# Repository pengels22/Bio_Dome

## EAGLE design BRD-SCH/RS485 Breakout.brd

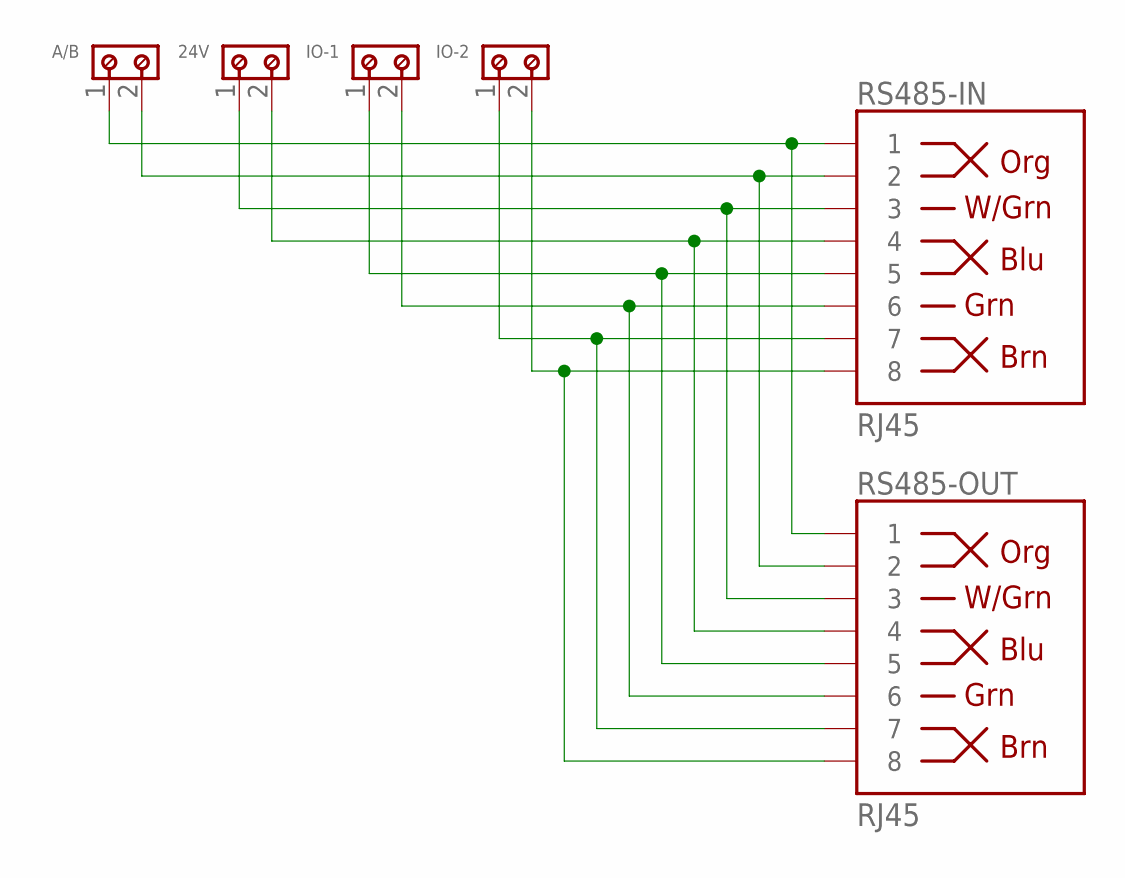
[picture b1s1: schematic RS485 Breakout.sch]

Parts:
24V: 691201520002
A/B: 691201520002
IO-1, IO-2: 691201520002
RS485-IN, RS485-OUT: RJ45; RJ45-8

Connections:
+24: 24V.1, RS485-IN.3, RS485-OUT.3
-24: 24V.2, RS485-IN.4, RS485-OUT.4
A: A/B.1, RS485-IN.1, RS485-OUT.1
B: A/B.2, RS485-IN.2, RS485-OUT.2
IO0: IO-1.2, RS485-IN.6, RS485-OUT.6
IO1: IO-1.1, RS485-IN.5, RS485-OUT.5
IO2: IO-2.2, RS485-IN.8, RS485-OUT.8
IO3: IO-2.1, RS485-IN.7, RS485-OUT.7

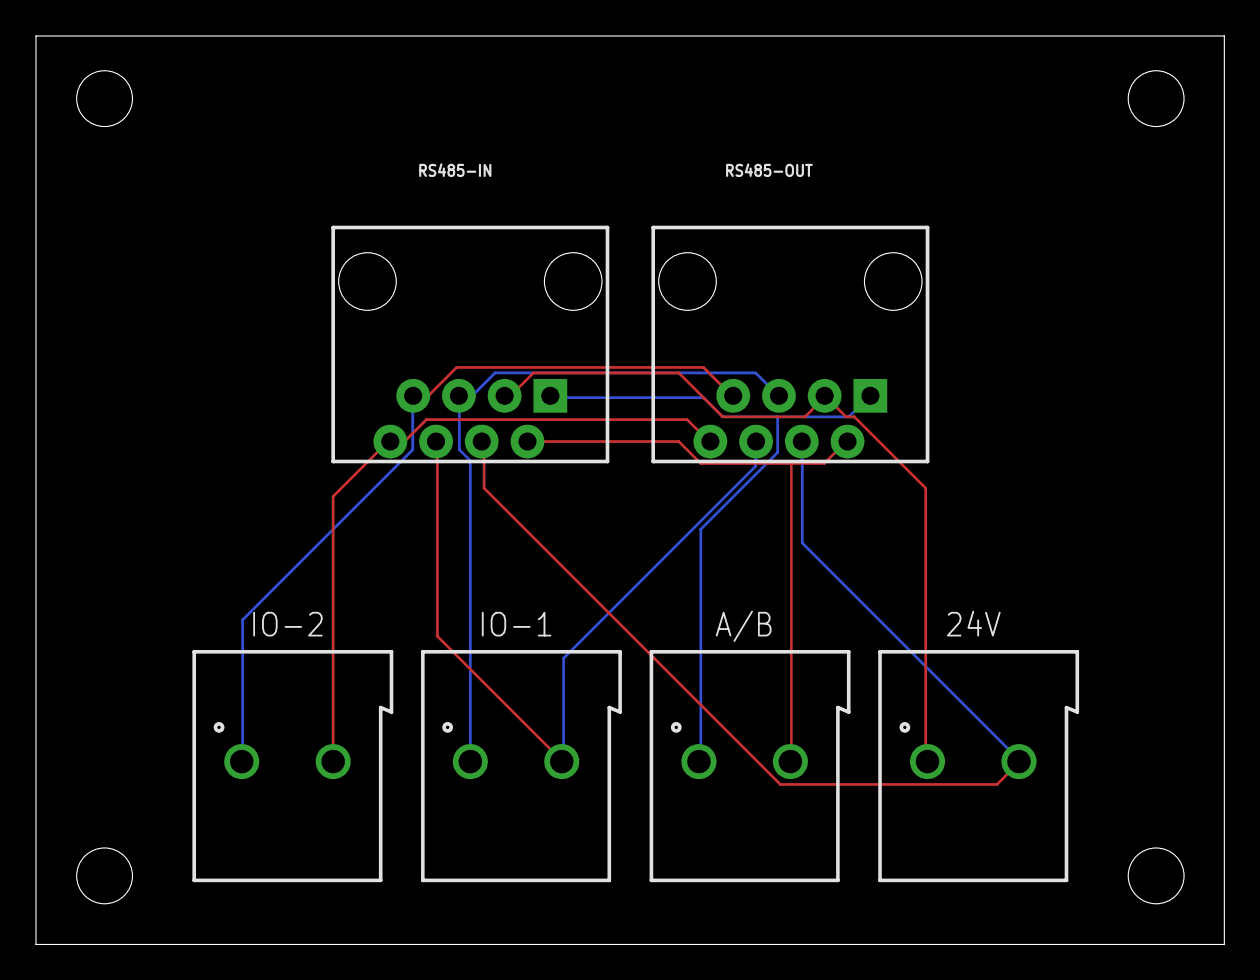
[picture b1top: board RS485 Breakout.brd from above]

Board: 2 copper layers, 66.0 x 50.5 mm, 6 parts (0 on the bottom side), 8 nets.

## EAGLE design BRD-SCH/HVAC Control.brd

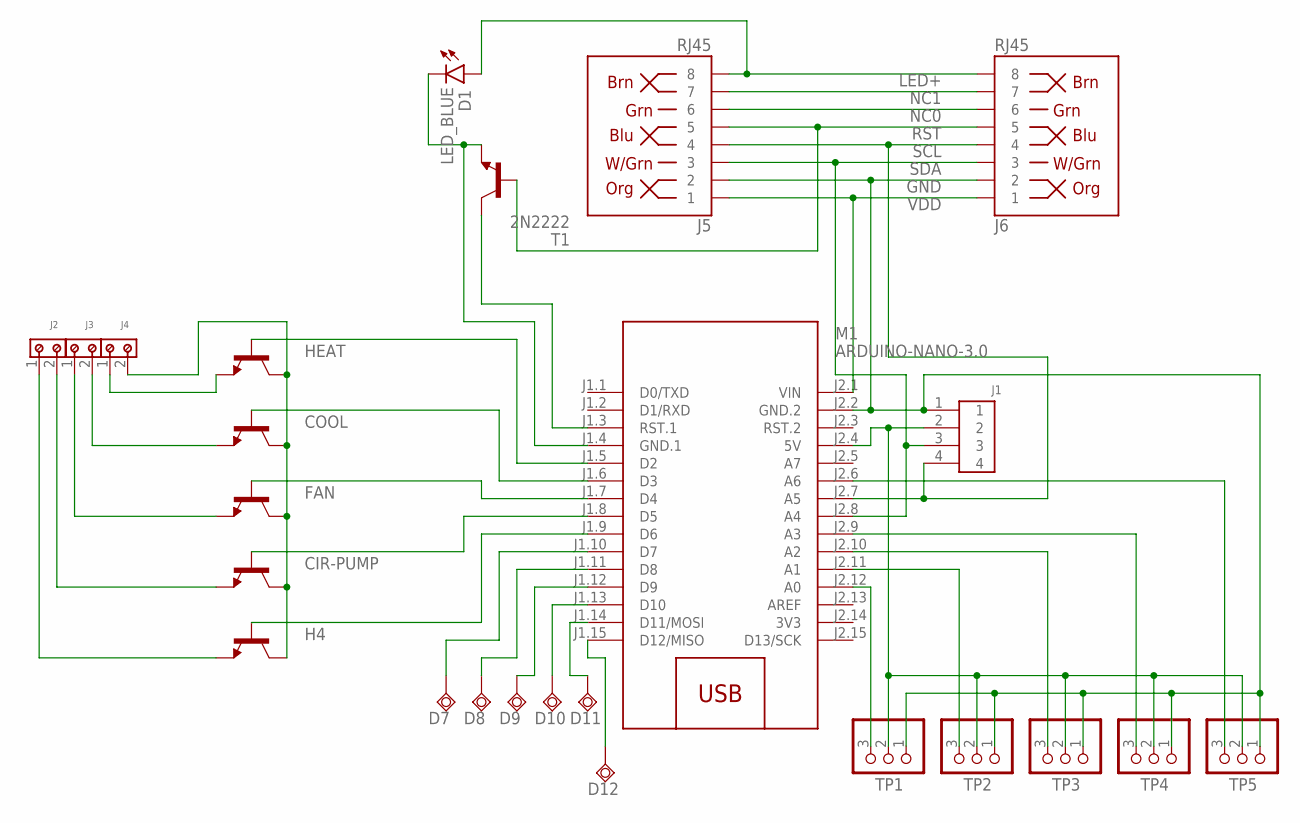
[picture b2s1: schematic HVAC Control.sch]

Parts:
CIR-PUMP: 600mA/40V; TO-92
COOL: 600mA/40V; TO-92
D1: LED_BLUE; LEDRD254W60D565H860B_B
D7, D8, D9, D10, D11, D12: TESTPAD_TPSQPAD1-13; TESTPAD_P1-13
FAN: 600mA/40V; TO-92
H4: 600mA/40V; TO-92
HEAT: 600mA/40V; TO-92
J1: B4B-XH-A(LF)(SN)
J2, J3, J4: 691201820002
J5, J6: RJ45; RJ45-8
M1: ARDUINO-NANO-3.0
T1: 2N2222; TO18
TP1, TP2, TP3, TP4, TP5: PINHD-1X3; 1X03

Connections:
3V3: M1.J2.14 (3V3)
GND: J1.1, J5.2, J6.2, M1.J2.2 (GND.2), M1.J2.3 (RST.2), TP1.1, TP2.1, TP3.1, TP4.1, TP5.1
LED+: D1.1 (A), J5.8, J6.8
unnamed: D7.TP, M1.J1.10 (D7)
unnamed: J1.2, M1.J2.4 (5V), TP1.2, TP2.2, TP3.2, TP4.2, TP5.2
unnamed: D8.TP, M1.J1.11 (D8)
unnamed: D9.TP, M1.J1.12 (D9)
unnamed: HEAT.2 (B), M1.J1.5 (D2)
unnamed: COOL.2 (B), M1.J1.6 (D3)
unnamed: FAN.2 (B), M1.J1.7 (D4)
unnamed: CIR-PUMP.2 (B), M1.J1.8 (D5)
unnamed: H4.2 (B), M1.J1.9 (D6)
unnamed: CIR-PUMP.1 (C), COOL.1 (C), FAN.1 (C), H4.1 (C), HEAT.1 (C), J4.2
unnamed: H4.3 (E), J2.1
unnamed: CIR-PUMP.3 (E), J2.2
unnamed: FAN.3 (E), J3.1
unnamed: COOL.3 (E), J3.2
unnamed: HEAT.3 (E), J4.1
unnamed: M1.J2.12 (A0), TP1.3
unnamed: M1.J2.11 (A1), TP2.3
unnamed: M1.J2.10 (A2), TP3.3
unnamed: M1.J2.9 (A3), TP4.3
unnamed: M1.J2.6 (A6), TP5.3
unnamed: M1.J1.3 (RST.1), T1.3 (C)
unnamed: D1.2 (C), M1.J1.4 (GND.1), T1.1 (E)
unnamed: D10.TP, M1.J1.13 (D10)
unnamed: D11.TP, M1.J1.14 (D11/MOSI)
unnamed: D12.TP, M1.J1.15 (D12/MISO)
NC0: J5.6, J6.6
NC1: J5.7, J6.7
RST: J5.5, J6.5, T1.2 (B)
SCL: J1.4, J5.4, J6.4, M1.J2.7 (A5)
SDA: J1.3, J5.3, J6.3, M1.J2.8 (A4)
VDD: J5.1, J6.1, M1.J2.1 (VIN)

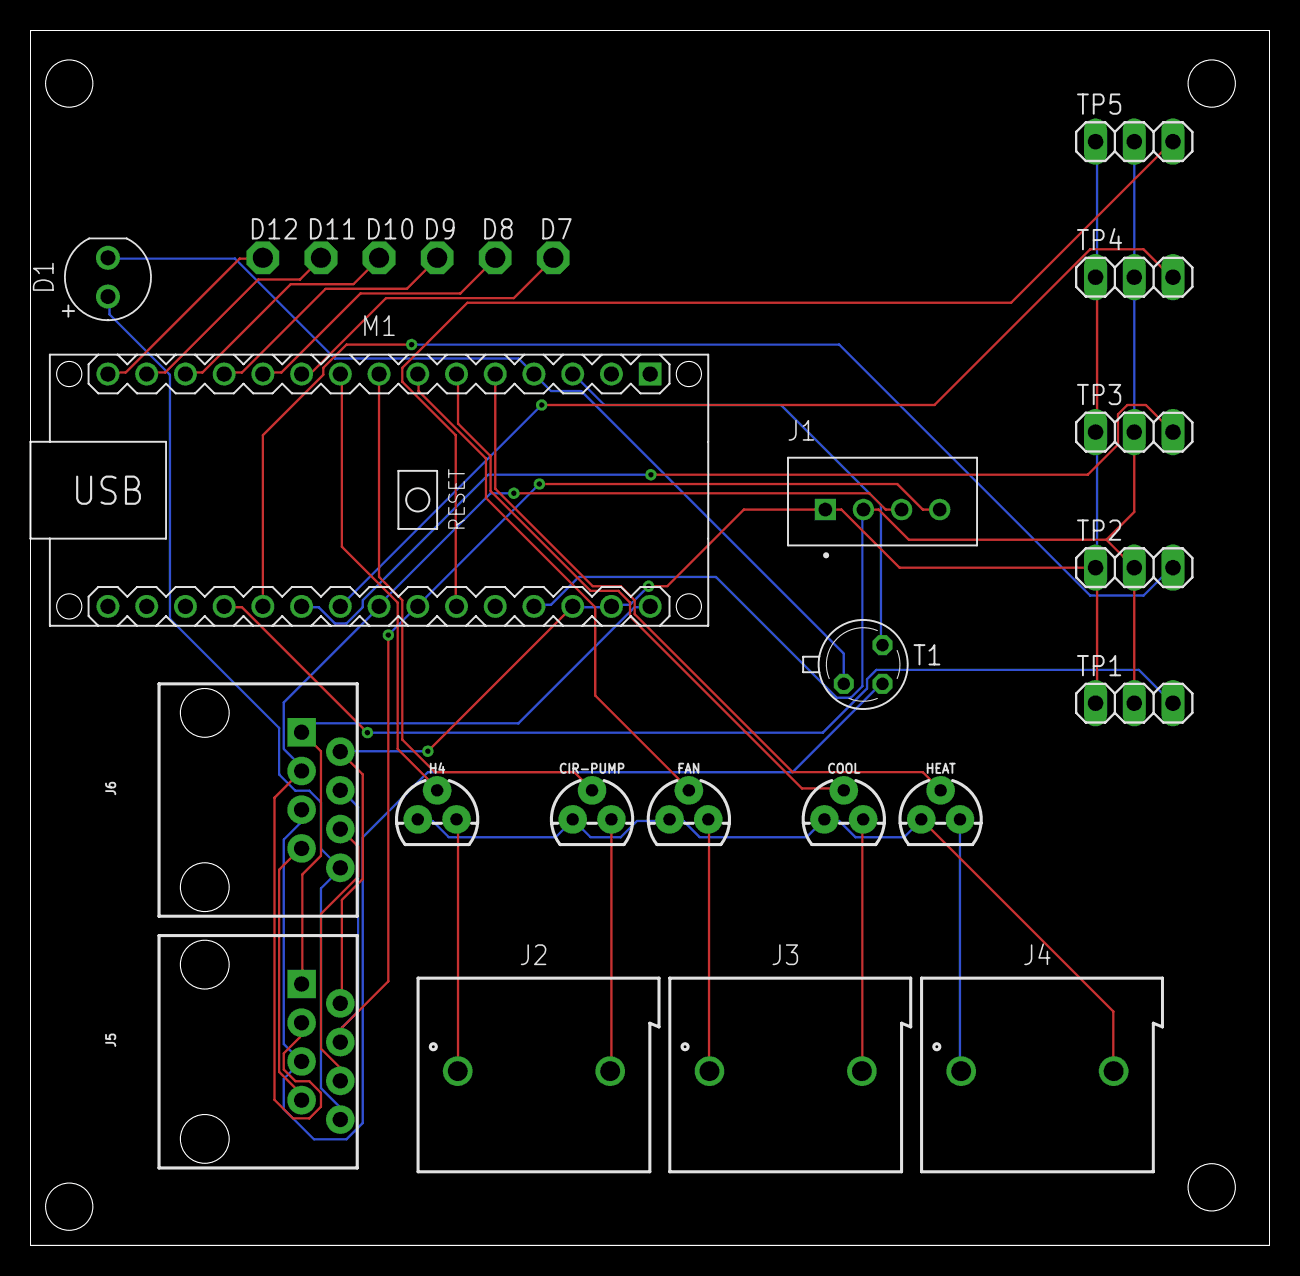
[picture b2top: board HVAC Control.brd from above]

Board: 2 copper layers, 81.3 x 79.7 mm, 25 parts (0 on the bottom side), 33 nets.

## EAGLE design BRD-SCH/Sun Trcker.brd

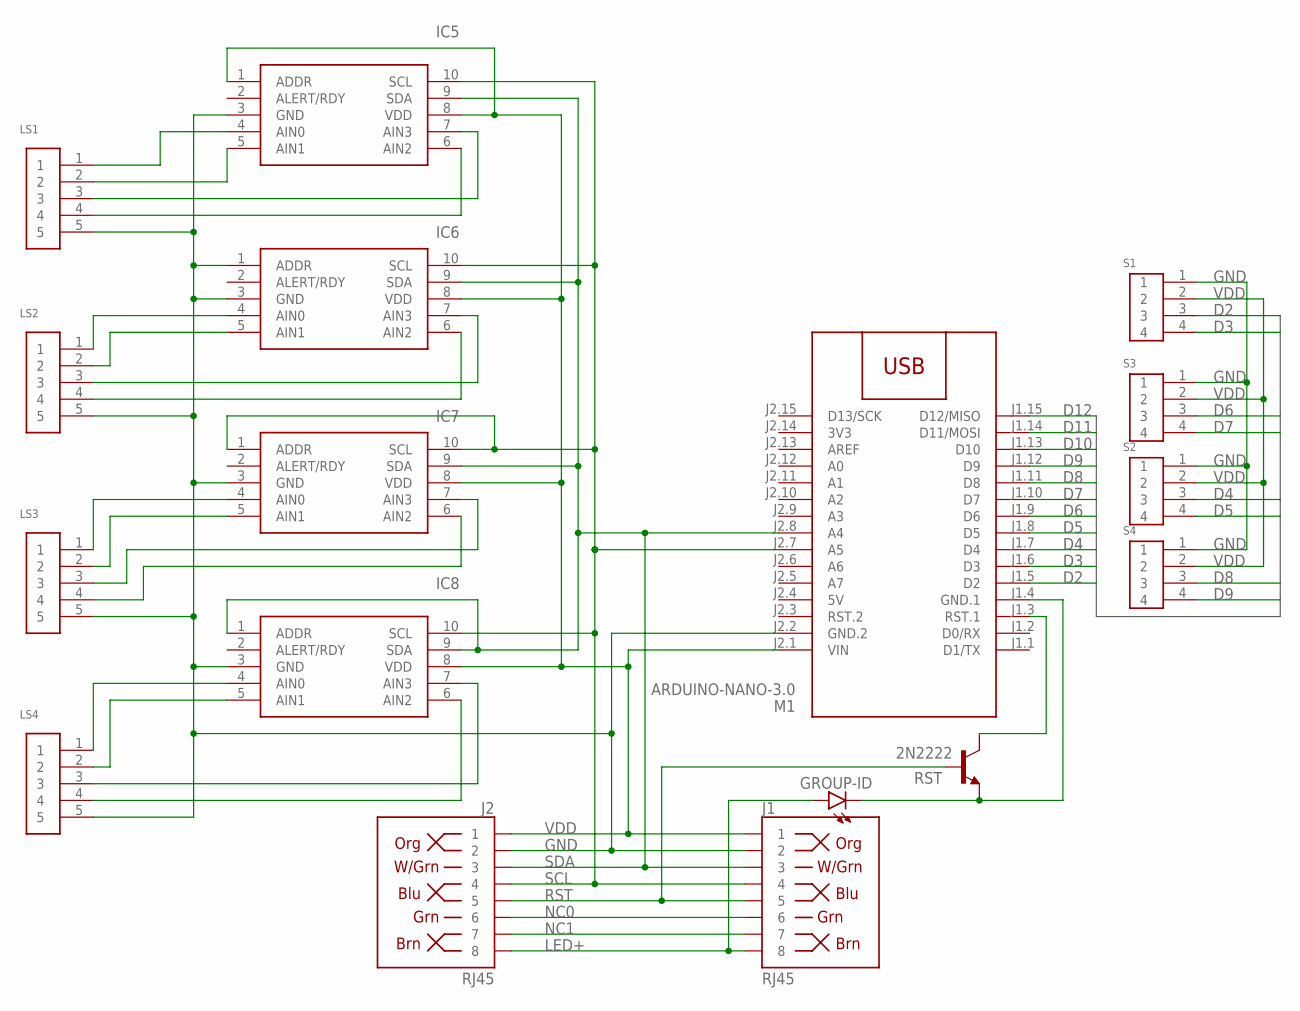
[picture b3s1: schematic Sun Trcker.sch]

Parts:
GROUP-ID: LED_BLUE; LEDRD254W60D565H860B_B
IC5, IC6, IC7, IC8: ADS1115IDGST; SOP50P490X110-10N
J1, J2: RJ45; RJ45-8
LS1, LS2, LS3, LS4: S5B-EH(LF)(SN)
M1: ARDUINO-NANO-3.0
RST: 2N2222; TO18
S1, S2, S3, S4: B4B-XH-A(LF)(SN)

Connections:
3V3: M1.J2.14 (3V3)
5V: M1.J2.4 (5V)
D2: M1.J1.5 (D2), S1.3
D3: M1.J1.6 (D3), S1.4
D4: M1.J1.7 (D4), S2.3
D5: M1.J1.8 (D5), S2.4
D6: M1.J1.9 (D6), S3.3
D7: M1.J1.10 (D7), S3.4
D8: M1.J1.11 (D8), S4.3
D9: M1.J1.12 (D9), S4.4
D10: M1.J1.13 (D10)
D11: M1.J1.14 (D11/MOSI)
D12: M1.J1.15 (D12/MISO)
GND: IC5.3 (GND), IC6.1 (ADDR), IC6.3 (GND), IC7.3 (GND), IC8.3 (GND), J1.2, J2.2, LS1.5, LS2.5, LS3.5, LS4.5, M1.J2.2 (GND.2), S1.1, S2.1, S3.1, S4.1
LED+: GROUP-ID.1 (A), J1.8, J2.8
unnamed: IC5.4 (AIN0), LS1.1
unnamed: IC5.5 (AIN1), LS1.2
unnamed: IC5.7 (AIN3), LS1.3
unnamed: IC5.6 (AIN2), LS1.4
unnamed: GROUP-ID.2 (C), M1.J1.4 (GND.1), RST.1 (E)
unnamed: IC6.4 (AIN0), LS2.1
unnamed: M1.J1.3 (RST.1), RST.3 (C)
unnamed: IC6.5 (AIN1), LS2.2
unnamed: IC6.7 (AIN3), LS2.3
unnamed: IC6.6 (AIN2), LS2.4
unnamed: IC7.4 (AIN0), LS3.1
unnamed: IC7.5 (AIN1), LS3.2
unnamed: IC7.7 (AIN3), LS3.3
unnamed: IC7.6 (AIN2), LS3.4
unnamed: IC8.4 (AIN0), LS4.1
unnamed: IC8.5 (AIN1), LS4.2
unnamed: IC8.7 (AIN3), LS4.3
unnamed: IC8.6 (AIN2), LS4.4
NC0: J1.6, J2.6
NC1: J1.7, J2.7
RST: J1.5, J2.5, RST.2 (B)
SCL: IC5.10 (SCL), IC6.10 (SCL), IC7.1 (ADDR), IC7.10 (SCL), IC8.10 (SCL), J1.4, J2.4, M1.J2.7 (A5)
SDA: IC5.9 (SDA), IC6.9 (SDA), IC7.9 (SDA), IC8.1 (ADDR), IC8.9 (SDA), J1.3, J2.3, M1.J2.8 (A4)
VDD: IC5.1 (ADDR), IC5.8 (VDD), IC6.8 (VDD), IC7.8 (VDD), IC8.8 (VDD), J1.1, J2.1, M1.J2.1 (VIN), S1.2, S2.2, S3.2, S4.2

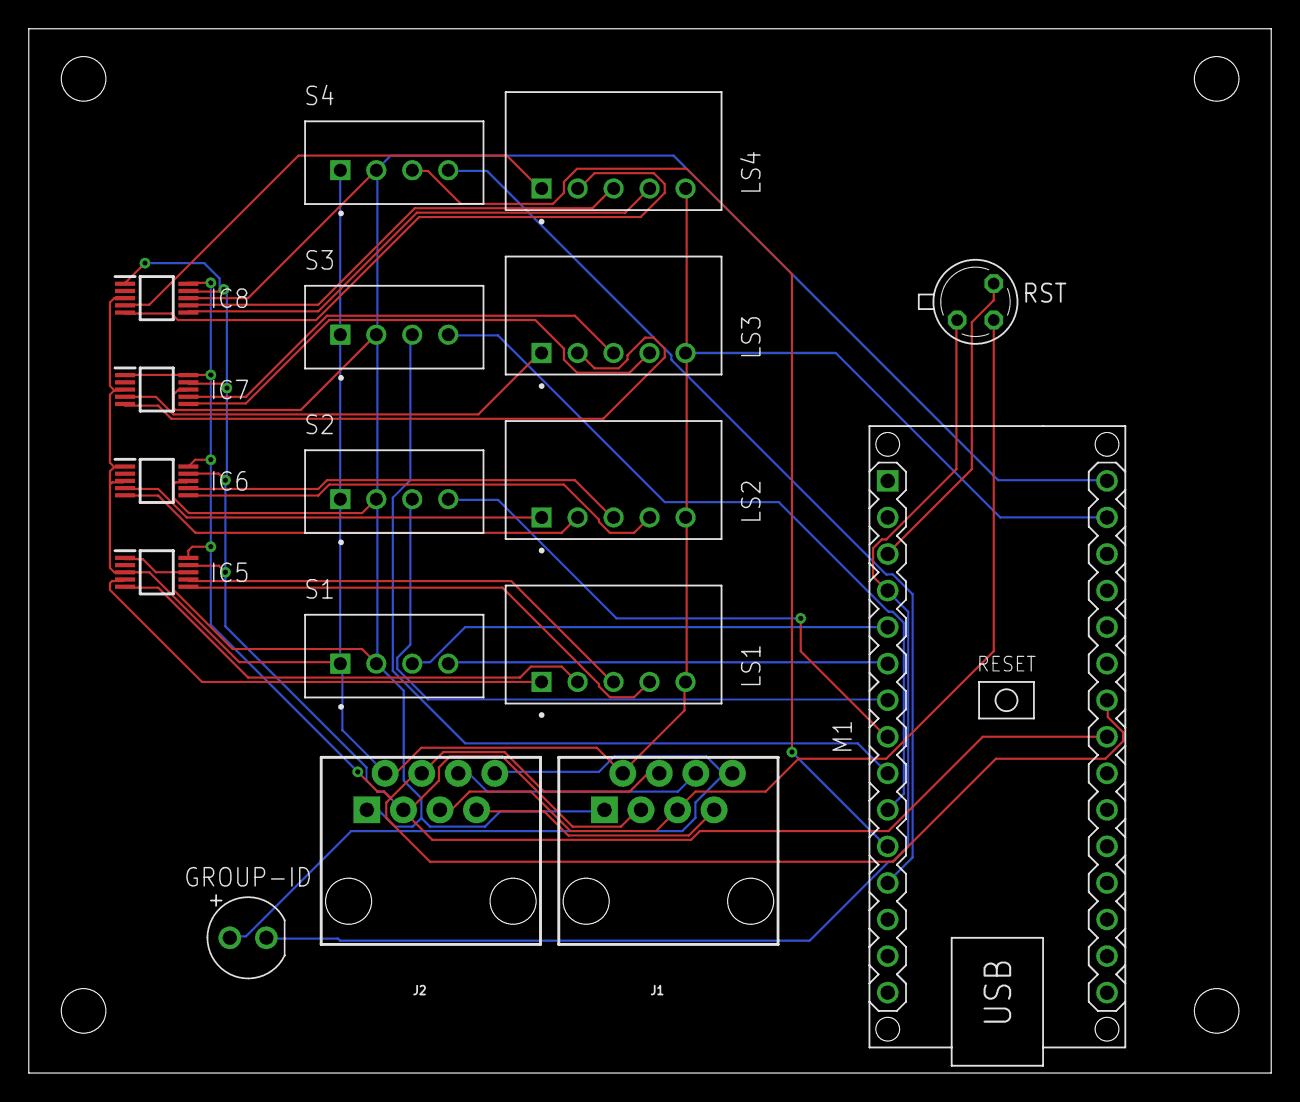
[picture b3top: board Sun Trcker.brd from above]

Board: 2 copper layers, 86.3 x 72.6 mm, 17 parts (0 on the bottom side), 34 nets.

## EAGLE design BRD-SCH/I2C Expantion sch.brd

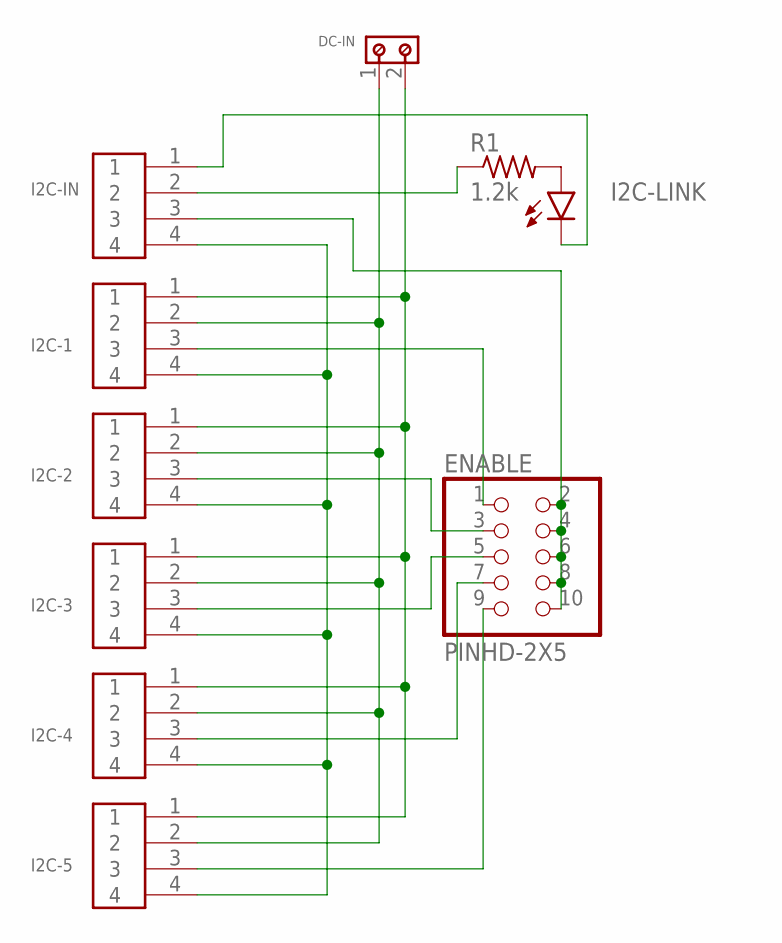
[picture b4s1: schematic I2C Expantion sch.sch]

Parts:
DC-IN: 691201620002
ENABLE: PINHD-2X5; 2X05
I2C-1, I2C-2, I2C-3, I2C-4, I2C-5, I2C-IN: B4B-XH-A(LF)(SN)
I2C-LINK: LED_BLUE; LEDRD254W60D565H860B_B
R1: 1.2k; RESAD724W46L381D178B

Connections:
GND: DC-IN.2, I2C-1.1, I2C-2.1, I2C-3.1, I2C-4.1, I2C-5.1
unnamed: I2C-LINK.1 (A), R1.2
unnamed: I2C-IN.2, R1.1
unnamed: I2C-IN.1, I2C-LINK.2 (C)
unnamed: ENABLE.9, I2C-5.3
unnamed: ENABLE.7, I2C-4.3
unnamed: ENABLE.5, I2C-3.3
unnamed: ENABLE.3, I2C-2.3
unnamed: ENABLE.1, I2C-1.3
SCL: I2C-1.4, I2C-2.4, I2C-3.4, I2C-4.4, I2C-5.4, I2C-IN.4
SDA: ENABLE.2, ENABLE.4, ENABLE.6, ENABLE.8, ENABLE.10, I2C-IN.3
VCC: DC-IN.1, I2C-1.2, I2C-2.2, I2C-3.2, I2C-4.2, I2C-5.2

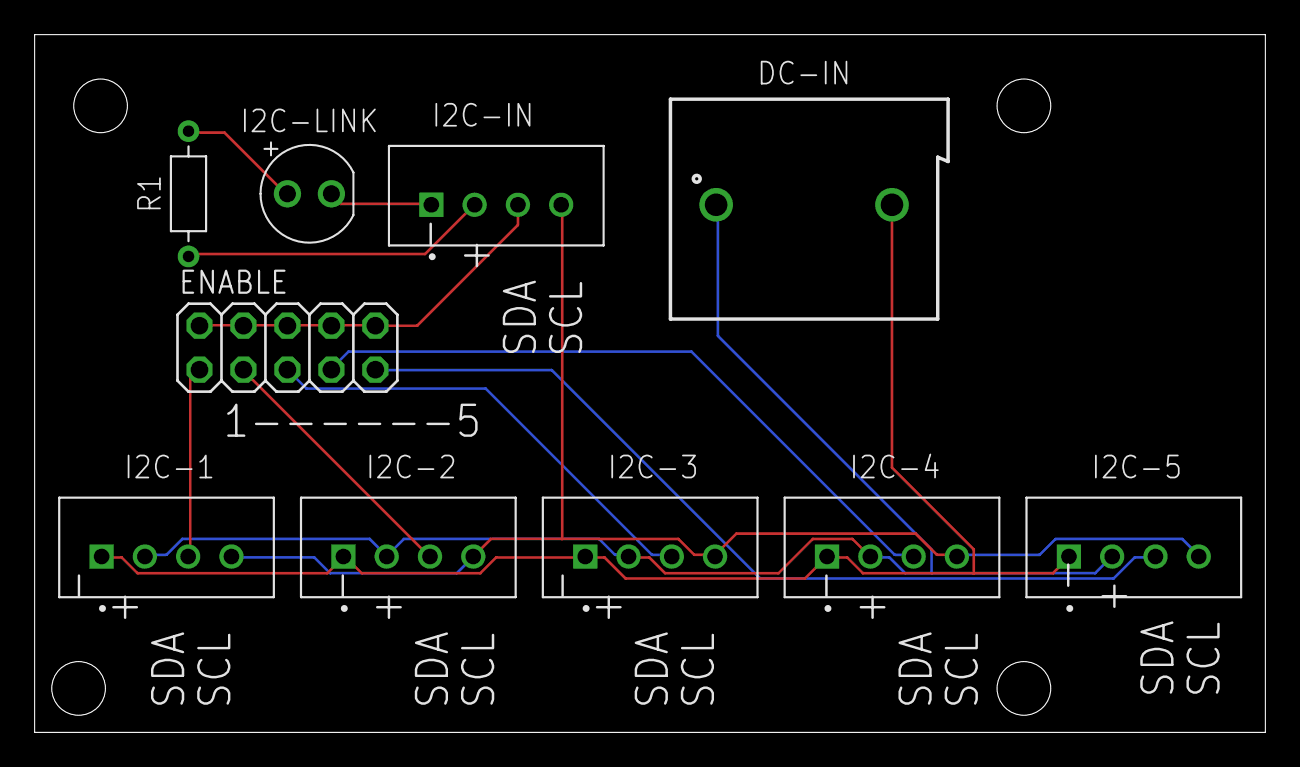
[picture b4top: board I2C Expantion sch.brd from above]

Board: 2 copper layers, 71.1 x 40.3 mm, 10 parts (0 on the bottom side), 12 nets.

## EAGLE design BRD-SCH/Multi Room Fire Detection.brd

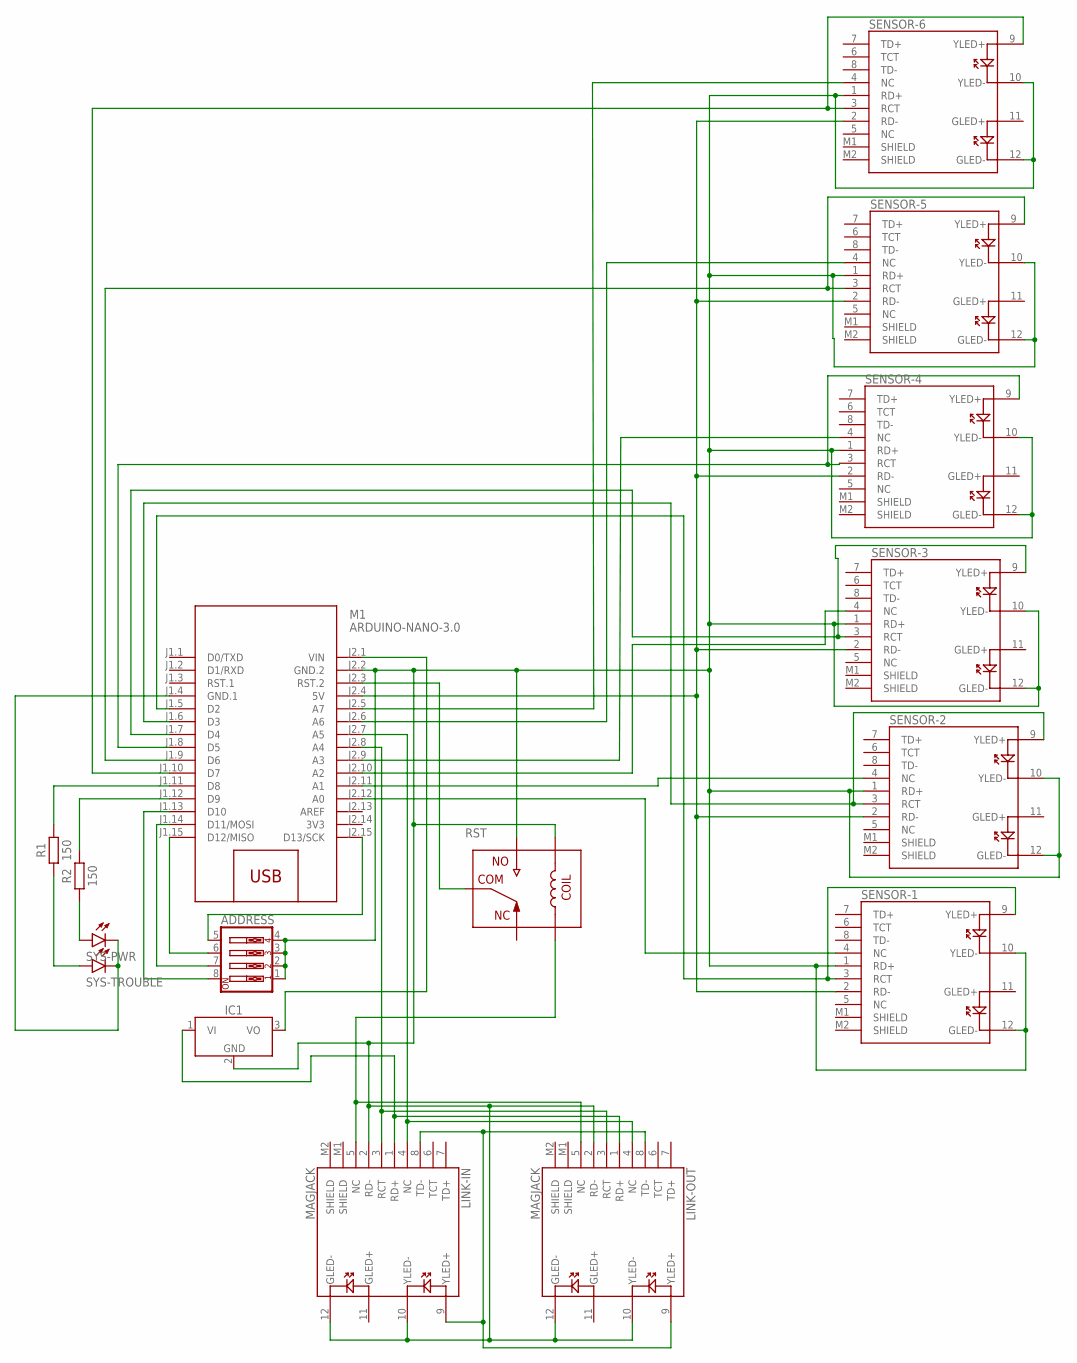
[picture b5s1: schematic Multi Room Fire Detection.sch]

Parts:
ADDRESS: SW_DIP-4; EDG-04
IC1: LM7805_TO220V; TO220V
LINK-IN: MAGJACK
LINK-OUT: MAGJACK
M1: ARDUINO-NANO-3.0
R1, R2: 150; RESAD724W46L381D178B
RST: ACT112
SENSOR-1, SENSOR-2, SENSOR-3, SENSOR-4, SENSOR-5, SENSOR-6: MAGJACK
SYS-PWR: LED_GREEN; LEDRD254W60D565H860B_G
SYS-TROUBLE: LED_RED; LEDRD254W60D565H860B

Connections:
3V3: M1.J2.14 (3V3)
GND: ADDRESS.1, ADDRESS.2, ADDRESS.3, ADDRESS.4, IC1.2 (GND), LINK-IN.2 (RD-), LINK-IN.10 (YLED-), LINK-IN.12 (GLED-), LINK-OUT.2 (RD-), LINK-OUT.10 (YLED-), LINK-OUT.12 (GLED-), M1.J2.2 (GND.2), RST.1, RST.4, SENSOR-1.1 (RD+), SENSOR-1.10 (YLED-), SENSOR-1.12 (GLED-), SENSOR-2.1 (RD+), SENSOR-2.10 (YLED-), SENSOR-2.12 (GLED-), SENSOR-3.1 (RD+), SENSOR-3.10 (YLED-), SENSOR-3.12 (GLED-), SENSOR-4.1 (RD+), SENSOR-4.10 (YLED-), SENSOR-4.12 (GLED-), SENSOR-5.1 (RD+), SENSOR-5.10 (YLED-), SENSOR-5.12 (GLED-), SENSOR-6.1 (RD+), SENSOR-6.10 (YLED-), SENSOR-6.12 (GLED-)
unnamed: M1.J2.12 (A0), SENSOR-1.4 (NC)
unnamed: M1.J2.11 (A1), SENSOR-2.4 (NC)
unnamed: M1.J2.10 (A2), SENSOR-3.4 (NC)
unnamed: M1.J2.9 (A3), SENSOR-4.4 (NC)
unnamed: M1.J2.6 (A6), SENSOR-5.4 (NC)
unnamed: M1.J2.5 (A7), SENSOR-6.4 (NC)
unnamed: M1.J1.10 (D7), SENSOR-6.3 (RCT), SENSOR-6.9 (YLED+)
unnamed: M1.J1.9 (D6), SENSOR-5.3 (RCT), SENSOR-5.9 (YLED+)
unnamed: M1.J1.8 (D5), SENSOR-4.3 (RCT), SENSOR-4.9 (YLED+)
unnamed: M1.J1.7 (D4), SENSOR-3.3 (RCT), SENSOR-3.9 (YLED+)
unnamed: M1.J1.6 (D3), SENSOR-2.3 (RCT), SENSOR-2.9 (YLED+)
unnamed: M1.J1.5 (D2), SENSOR-1.3 (RCT), SENSOR-1.9 (YLED+)
unnamed: M1.J2.4 (5V), SENSOR-1.2 (RD-), SENSOR-2.2 (RD-), SENSOR-3.2 (RD-), SENSOR-4.2 (RD-), SENSOR-5.2 (RD-), SENSOR-6.2 (RD-)
unnamed: M1.J2.3 (RST.2), RST.2
unnamed: LINK-IN.3 (RCT), LINK-OUT.3 (RCT), M1.J2.8 (A4)
unnamed: LINK-IN.4 (NC), LINK-OUT.4 (NC), M1.J2.7 (A5)
unnamed: LINK-IN.5 (NC), LINK-OUT.5 (NC), RST.5
unnamed: M1.J1.11 (D8), R1.2
unnamed: M1.J1.12 (D9), R2.2
unnamed: R1.1, SYS-TROUBLE.1 (A)
unnamed: M1.J1.4 (GND.1), SYS-PWR.2 (C), SYS-TROUBLE.2 (C)
unnamed: R2.1, SYS-PWR.1 (A)
unnamed: ADDRESS.5, M1.J2.15 (D13/SCK)
unnamed: ADDRESS.6, M1.J1.15 (D12/MISO)
unnamed: ADDRESS.7, M1.J1.14 (D11/MOSI)
unnamed: ADDRESS.8, M1.J1.13 (D10)
unnamed: LINK-IN.8 (TD-), LINK-IN.9 (YLED+), LINK-OUT.8 (TD-), LINK-OUT.9 (YLED+)
VI: IC1.1 (VI), LINK-IN.1 (RD+), LINK-OUT.1 (RD+)
VO: IC1.3 (VO), M1.J2.1 (VIN)

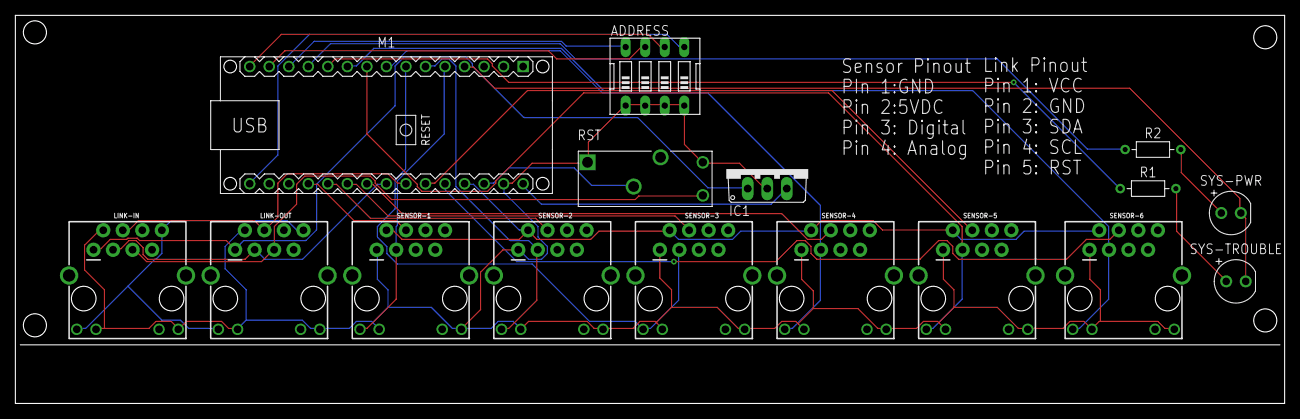
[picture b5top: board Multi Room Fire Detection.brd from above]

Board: 2 copper layers, 165.1 x 50.5 mm, 16 parts (0 on the bottom side), 30 nets.

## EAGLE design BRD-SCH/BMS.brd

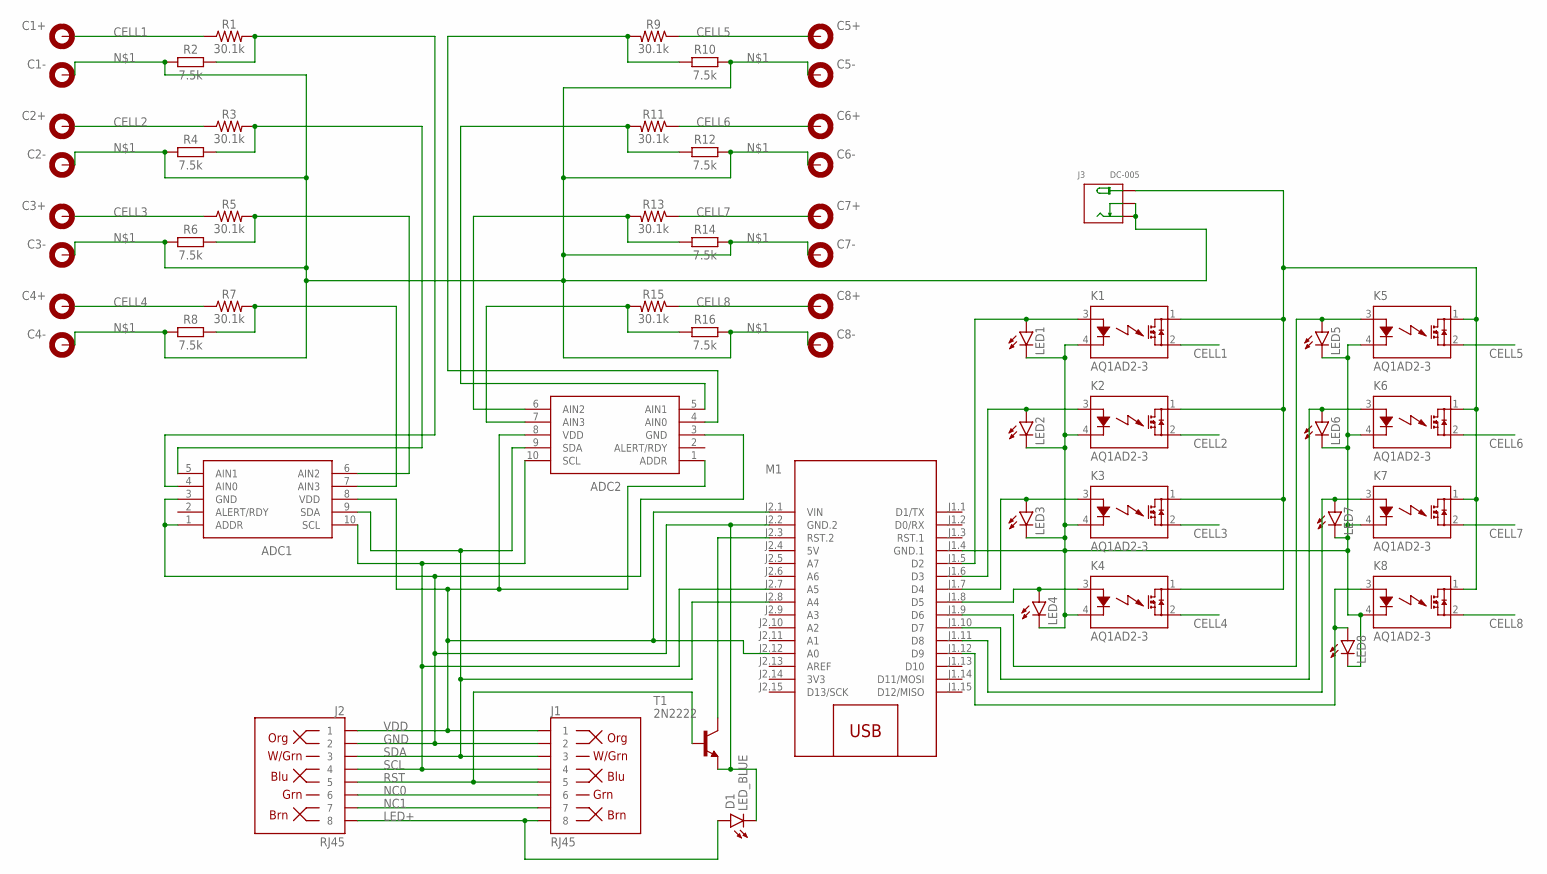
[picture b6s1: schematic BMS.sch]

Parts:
ADC1, ADC2: ADS1115IDGST; SOP50P490X110-10N
C1+, C1-, C2+, C2-, C3+, C3-, C4+, C4-, C5+, C5-, C6+, C6-, C7+, C7-, C8+, C8-: HOLES_MOUNT-PAD-ROUND-0.096-NS; HOLES_096-PAD-NS
D1: LED_BLUE; LEDRD254W60D565H860B_B
J1, J2: RJ45; RJ45-8
J3: DC-005; DCJ3P-14.2X11.0X9.0MM
K1, K2, K3, K4, K5, K6, K7, K8: AQ1AD2-3; AQ1
LED1, LED2, LED3, LED4, LED5, LED6, LED7, LED8: LEDCHIP-LED0805; CHIP-LED0805
M1: ARDUINO-NANO-3.0
R1, R3, R5, R7, R9, R11, R13, R15: 30.1k; 0603
R2, R4, R6, R8, R10, R12, R14, R16: 7.5k; RESC3216X70
T1: 2N2222; TO18

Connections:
3V3: M1.J2.14 (3V3)
5V: M1.J2.4 (5V)
C+: J3.+B (+), J3.+T (+), K1.1 (DS1), K2.1 (DS1), K3.1 (DS1), K4.1 (DS1), K5.1 (DS1), K6.1 (DS1), K7.1 (DS1), K8.1 (DS1)
CELL1: C1+.B096, K1.2 (DS2), R1.1
CELL2: C2+.B096, K2.2 (DS2), R3.1
CELL3: C3+.B096, K3.2 (DS2), R5.1
CELL4: C4+.B096, K4.2 (DS2), R7.1
CELL5: C5+.B096, K5.2 (DS2), R9.1
CELL6: C6+.B096, K6.2 (DS2), R11.1
CELL7: C7+.B096, K7.2 (DS2), R13.1
CELL8: C8+.B096, K8.2 (DS2), R15.1
GND: ADC1.1 (ADDR), ADC1.3 (GND), ADC2.3 (GND), D1.2 (C), J1.2, J2.2, M1.J2.2 (GND.2), T1.1 (E)
LED+: D1.1 (A), J1.8, J2.8
unnamed: C1-.B096, C2-.B096, C3-.B096, C4-.B096, C5-.B096, C6-.B096, C7-.B096, C8-.B096, J3.-1B (-), J3.-1T (-), J3.-2 (CDN), J3.-2B (CDN), R2.1, R4.1, R6.1, R8.1, R10.1, R12.1, R14.1, R16.1
unnamed: ADC1.7 (AIN3), R7.2, R8.2
unnamed: M1.J2.3 (RST.2), T1.3 (C)
unnamed: K1.3 (A), LED1.A, M1.J1.5 (D2)
unnamed: K2.3 (A), LED2.A, M1.J1.6 (D3)
unnamed: K3.3 (A), LED3.A, M1.J1.7 (D4)
unnamed: K4.3 (A), LED4.A, M1.J1.8 (D5)
unnamed: K5.3 (A), LED5.A, M1.J1.9 (D6)
unnamed: K6.3 (A), LED6.A, M1.J1.10 (D7)
unnamed: K7.3 (A), LED7.A, M1.J1.11 (D8)
unnamed: K8.3 (A), LED8.A, M1.J1.12 (D9)
unnamed: K1.4 (K), K2.4 (K), K3.4 (K), K4.4 (K), K5.4 (K), K6.4 (K), K7.4 (K), K8.4 (K), LED1.C, LED2.C, LED3.C, LED4.C, LED5.C, LED6.C, LED7.C, LED8.C, M1.J1.4 (GND.1)
unnamed: ADC1.6 (AIN2), R5.2, R6.2
unnamed: ADC1.5 (AIN1), R3.2, R4.2
unnamed: ADC1.4 (AIN0), R1.2, R2.2
unnamed: ADC2.7 (AIN3), R15.2, R16.2
unnamed: ADC2.6 (AIN2), R13.2, R14.2
unnamed: ADC2.5 (AIN1), R11.2, R12.2
unnamed: ADC2.4 (AIN0), R9.2, R10.2
NC0: J1.6, J2.6
NC1: J1.7, J2.7
RST: J1.5, J2.5, T1.2 (B)
SCL: ADC1.10 (SCL), ADC2.10 (SCL), J1.4, J2.4, M1.J2.7 (A5)
SDA: ADC1.9 (SDA), ADC2.9 (SDA), J1.3, J2.3, M1.J2.8 (A4)
VDD: ADC1.8 (VDD), ADC2.1 (ADDR), ADC2.8 (VDD), J1.1, J2.1, M1.J2.1 (VIN), M1.J2.12 (A0)

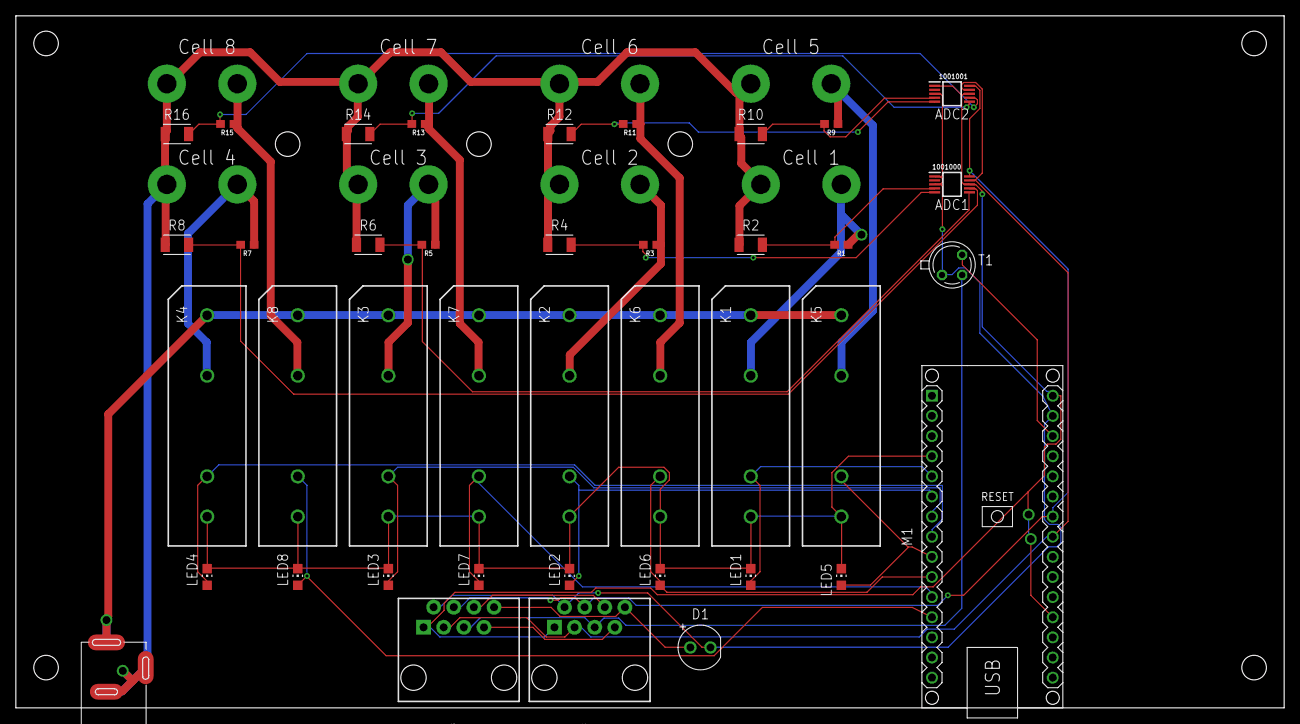
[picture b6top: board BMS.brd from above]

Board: 2 copper layers, 159.9 x 87.2 mm, 56 parts (0 on the bottom side), 36 nets.

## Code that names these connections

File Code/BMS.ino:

#include <Adafruit_ADS1X15.h>
Adafruit_ADS1115 ads1;
Adafruit_ADS1115 ads2;

int adc0 = 0;
int adc1 = 0;
int adc2 = 0;
int adc3 = 0;

int adc4 = 0;
int adc5 = 0;
int adc6 = 0;
int adc7 = 0;
int volt8 = 0;

int Cell1 = 2;
int Cell2 = 3;
int Cell3 = 4;
int Cell4 = 5;
int Cell5 = 6;
int Cell6 = 7;
int Cell7 = 8;
int Cell8 = 9;
float volts0, volts1, volts2, volts3, volts4, volts5, volts6, volts7;

void setup() {
  // put your setup code here, to run once:
  ads1.begin(0x48);
  ads2.begin(0x49);
  pinMode(Cell1, OUTPUT);
  pinMode(Cell2, OUTPUT);
  pinMode(Cell3, OUTPUT);
  pinMode(Cell4, OUTPUT);
  pinMode(Cell5, OUTPUT);
  pinMode(Cell6, OUTPUT);
  pinMode(Cell7, OUTPUT);
  pinMode(Cell8, OUTPUT);
  Serial.begin(9600);
}

void loop() {
  // put your main code here, to run repeatedly:

  volt8 = analogRead(A0);
  volt8 = map(volt8, 0, 1023, 0, 5) * 5;
  if (volt8 > 10) {
    adc0 = ads1.readADC_SingleEnded(0);
    adc1 = ads1.readADC_SingleEnded(1);
    adc2 = ads1.readADC_SingleEnded(2);
    adc3 = ads1.readADC_SingleEnded(3);
    volts0 = ads1.computeVolts(adc0);
    volts1 = ads1.computeVolts(adc1);
    volts2 = ads1.computeVolts(adc2);
    volts3 = ads1.computeVolts(adc3);

    adc4 = ads2.readADC_SingleEnded(0);
    adc5 = ads2.readADC_SingleEnded(1);
    adc6 = ads2.readADC_SingleEnded(2);
    adc7 = ads2.readADC_SingleEnded(3);
    volts4 = ads2.computeVolts(adc4);
    volts5 = ads2.computeVolts(adc5);
    volts6 = ads2.computeVolts(adc6);
    volts7 = ads2.computeVolts(adc7);
    volts0 = volts0 * 5;
    volts1 = volts1 * 5;
    volts2 = volts2 * 5;
    volts3 = volts3 * 5;
    volts4 = volts4 * 5;
    volts5 = volts5 * 5;
    volts6 = volts6 * 5;
    volts7 = volts7 * 5;
    if (volts0 < 10) {
      digitalWrite(Cell1, HIGH);
    }
    else {
      digitalWrite(Cell1, LOW);
    }

    if (volts1 < 10) {
      digitalWrite(Cell2, HIGH);
    }
    else {
      digitalWrite(Cell2, LOW);
    }
    if (volts2 < 10) {
      digitalWrite(Cell3, HIGH);
    }
    else {
      digitalWrite(Cell3, LOW);
    }
    if (volts3 < 10) {
      digitalWrite(Cell4, HIGH);
    }
    else {
      digitalWrite(Cell4, LOW);
    }

    if (volts4 < 10) {
      digitalWrite(Cell5, HIGH);
    }
    else {
      digitalWrite(Cell5, LOW);
    }
    if (volts5 < 10) {
      digitalWrite(Cell6, HIGH);
    }
    else {
      digitalWrite(Cell6, LOW);
    }

    if (volts6 < 10) {
      digitalWrite(Cell7, HIGH);
    }
    else {
      digitalWrite(Cell7, LOW);
    }
    if (volts7 < 10) {
      digitalWrite(Cell8, HIGH);
    }
    else {
      digitalWrite(Cell8, LOW);
    }


    if (volts0 > 12) {
      digitalWrite(Cell1, LOW);
    }
    else {
      digitalWrite(Cell1, HIGH);
    }

    if (volts1 > 12) {
      digitalWrite(Cell2, LOW);
    }
    else {
      digitalWrite(Cell2, HIGH);
    }

    if (volts2 > 12) {
      digitalWrite(Cell3, LOW);
    }
    else {
      digitalWrite(Cell3, HIGH);
    }

    if (volts3 > 12) {
      digitalWrite(Cell4, LOW);
    }
    else {
      digitalWrite(Cell4, HIGH);
    }

    if (volts4 > 12) {
      digitalWrite(Cell5, LOW);
    }
    else {
      digitalWrite(Cell5, HIGH);
    }

    if (volts5 > 12) {
      digitalWrite(Cell6, LOW);
    }
    else {
      digitalWrite(Cell6, HIGH);
    }

    if (volts6 > 12) {
      digitalWrite(Cell7, LOW);
    }
    else {
      digitalWrite(Cell7, HIGH);
    }
    if (volts7 > 12) {
      digitalWrite(Cell8, LOW);
    }
    else {
      digitalWrite(Cell8, HIGH);
    }


  }
  adc0 = ads1.readADC_SingleEnded(0);
  adc1 = ads1.readADC_SingleEnded(1);
  adc2 = ads1.readADC_SingleEnded(2);
  adc3 = ads1.readADC_SingleEnded(3);
  volts0 = ads1.computeVolts(adc0);
  volts1 = ads1.computeVolts(adc1);
  volts2 = ads1.computeVolts(adc2);
  volts3 = ads1.computeVolts(adc3);

  adc4 = ads2.readADC_SingleEnded(0);
  adc5 = ads2.readADC_SingleEnded(1);
  adc6 = ads2.readADC_SingleEnded(2);
  adc7 = ads2.readADC_SingleEnded(3);
  volts4 = ads2.computeVolts(adc4);
  volts5 = ads2.computeVolts(adc5);
  volts6 = ads2.computeVolts(adc6);
  volts7 = ads2.computeVolts(adc7);
  volts0 = volts0 * 5;
  volts1 = volts1 * 5;
  volts2 = volts2 * 5;
  volts3 = volts3 * 5;
  volts4 = volts4 * 5;
  volts5 = volts5 * 5;
  volts6 = volts6 * 5;
  volts7 = volts7 * 5;
  Serial.println(volts0);
  Serial.println(volts1);
  Serial.println(volts2);
  Serial.println(volts3);
  Serial.println(volts4);
  Serial.println(volts5);
  Serial.println(volts6);
  Serial.println(volts7);
}

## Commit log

2022-09-26 Bio Main
2022-09-30 RS485 Breakout
    Breakout for ethernet to RS485 For VFD Control

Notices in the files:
parts and their libraries:
SparkFun-Connectors: Licensing: Creative Commons ShareAlike 4.0 International - https://creativecommons.org/licenses/by-sa/4.0
diy-modules: Released under the Creative Commons Attribution 4.0 International License: http://creativecommons.org/licenses/by/4.0
